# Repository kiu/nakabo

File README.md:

# nakabo

Welcome to *nakabo* - a collection of neatly designed breakout boards aimed at simplifying development and experimentation.

Feel free to give me a shoutout [@kiu112](https://twitter.com/kiu112) - I would love to see how my [#nakabo](https://twitter.com/search?q=%2523nakabo) boards are being used in your projects.

# nakabo-avr64*

* All pins routed out to headers / sockets
* AVR6 IDC connector (6P 2x03 2.54mm / 100mil) for UPDI programming and debugging
* Major pin functions documented on front silkscreen
* 2.54mm / 100mil breadboard compatible spacing
* Dedicated reset button
* [FT232RL module](https://www.amazon.de/s?k=FT232RL+module) compatible pin socket for easy serial interfacing

Disclaimer: These are not plug and play development boards - you need an UPDI compatible programmer to use them. There is no protection (e.g. reverse polarity), handle with care.

## nakabo-avr64da32

*nakabo-avr64da32* is a break-out board for the [AVR64DA32](https://www.microchip.com/en-us/product/AVR64DA32) microcontroller.

(Hint: stencil is identical to *nakabo-avr64ea32*)

## nakabo-avr64db32

*nakabo-avr64db32* is a break-out board for the [AVR64DB32](https://www.microchip.com/en-us/product/AVR64DB32) microcontroller.

(Hint: stencil is identical to *nakabo-avr64dd32*)

## nakabo-avr64dd32

*nakabo-avr64dd32* is a break-out board for the [AVR64DD32](https://www.microchip.com/en-us/product/AVR64DD32) microcontroller.

(Hint: stencil is identical to *nakabo-avr64db32*)

## nakabo-avr64ea32

*nakabo-avr64ea32* is a break-out board for the [AVR64EA32](https://www.microchip.com/en-us/product/AVR64EA32) microcontroller.

(Hint: stencil is identical to *nakabo-avr64da32*)

# License

This project is licensed under the Creative Commons Attribution-NonCommercial 3.0 Unported (CC BY-NC 3.0) license.

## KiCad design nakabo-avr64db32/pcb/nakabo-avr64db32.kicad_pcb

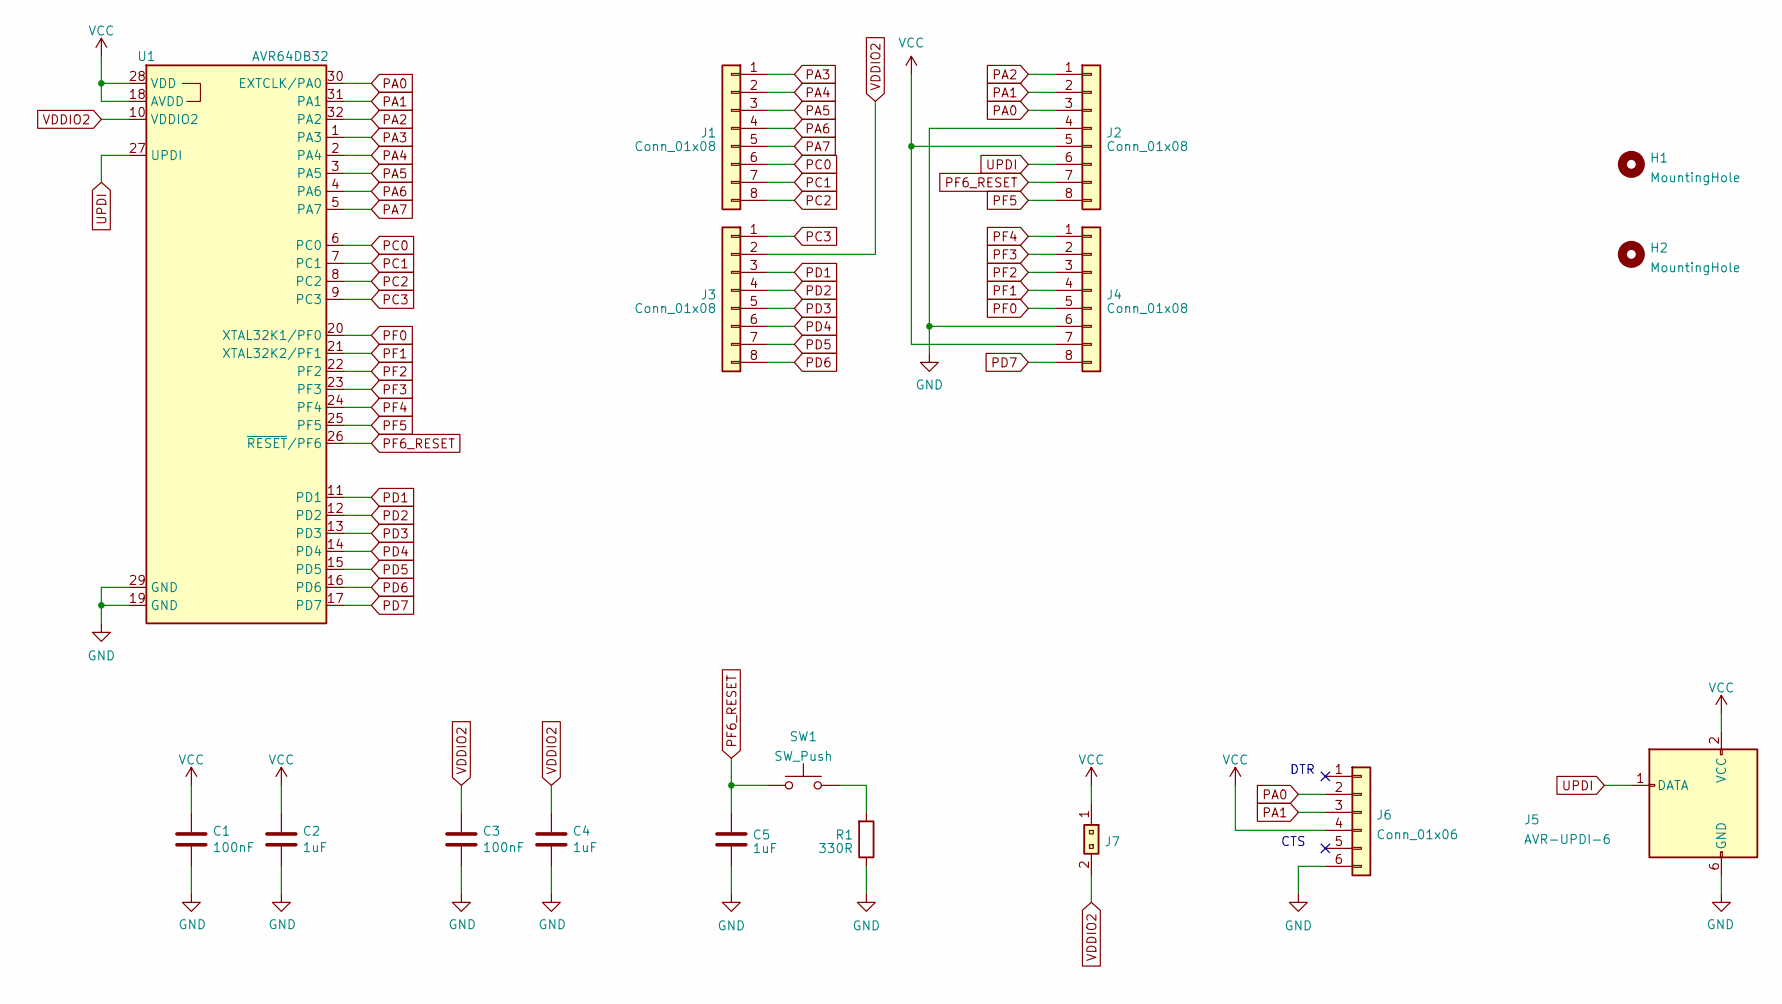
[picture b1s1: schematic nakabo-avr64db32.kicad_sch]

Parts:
C1, C3: 100nF; C_0805_2012Metric
C2, C4, C5: 1uF; C_0805_2012Metric
H1, H2: MountingHole; MountingHole_3.2mm_M3_DIN965
J1, J2, J3, J4: Conn_01x08; PinSocket_1x08_P2.54mm_Vertical
J5: AVR-UPDI-6; IDC-Header_2x03_P2.54mm_Vertical
J6: Conn_01x06; PinSocket_1x06_P2.54mm_Vertical
J7: 1x02_Jumper; PinHeader_1x02_P2.54mm_Vertical
R1: 330R; R_0805_2012Metric
SW1: SW_Push; SW_Push_1P1T_NO_4.5x4.5mm
U1: AVR64DB32; TQFP-32_7x7mm_P0.8mm

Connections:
GND: C1.2, C2.2, C3.2, C4.2, C5.2, J2.4, J4.6, J5.6 (GND), J6.6, R1.1, U1.19 (GND), U1.29 (GND)
unnamed: R1.2, SW1.2
PA0: J2.3, J6.2, U1.30 (EXTCLK/PA0)
PA1: J2.2, J6.3, U1.31 (PA1)
PA2: J2.1, U1.32 (PA2)
PA3: J1.1, U1.1 (PA3)
PA4: J1.2, U1.2 (PA4)
PA5: J1.3, U1.3 (PA5)
PA6: J1.4, U1.4 (PA6)
PA7: J1.5, U1.5 (PA7)
PC0: J1.6, U1.6 (PC0)
PC1: J1.7, U1.7 (PC1)
PC2: J1.8, U1.8 (PC2)
PC3: J3.1, U1.9 (PC3)
PD1: J3.3, U1.11 (PD1)
PD2: J3.4, U1.12 (PD2)
PD3: J3.5, U1.13 (PD3)
PD4: J3.6, U1.14 (PD4)
PD5: J3.7, U1.15 (PD5)
PD6: J3.8, U1.16 (PD6)
PD7: J4.8, U1.17 (PD7)
PF0: J4.5, U1.20 (XTAL32K1/PF0)
PF1: J4.4, U1.21 (XTAL32K2/PF1)
PF2: J4.3, U1.22 (PF2)
PF3: J4.2, U1.23 (PF3)
PF4: J4.1, U1.24 (PF4)
PF5: J2.8, U1.25 (PF5)
PF6_RESET: C5.1, J2.7, SW1.1, U1.26 (~RESET/PF6)
UPDI: J2.6, J5.1 (DATA), U1.27 (UPDI)
VCC: C1.1, C2.1, J2.5, J4.7, J5.2 (VCC), J6.4, J7.1, U1.18 (AVDD), U1.28 (VDD)
VDDIO2: C3.1, C4.1, J3.2, J7.2, U1.10 (VDDIO2)

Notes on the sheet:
DTR
CTS

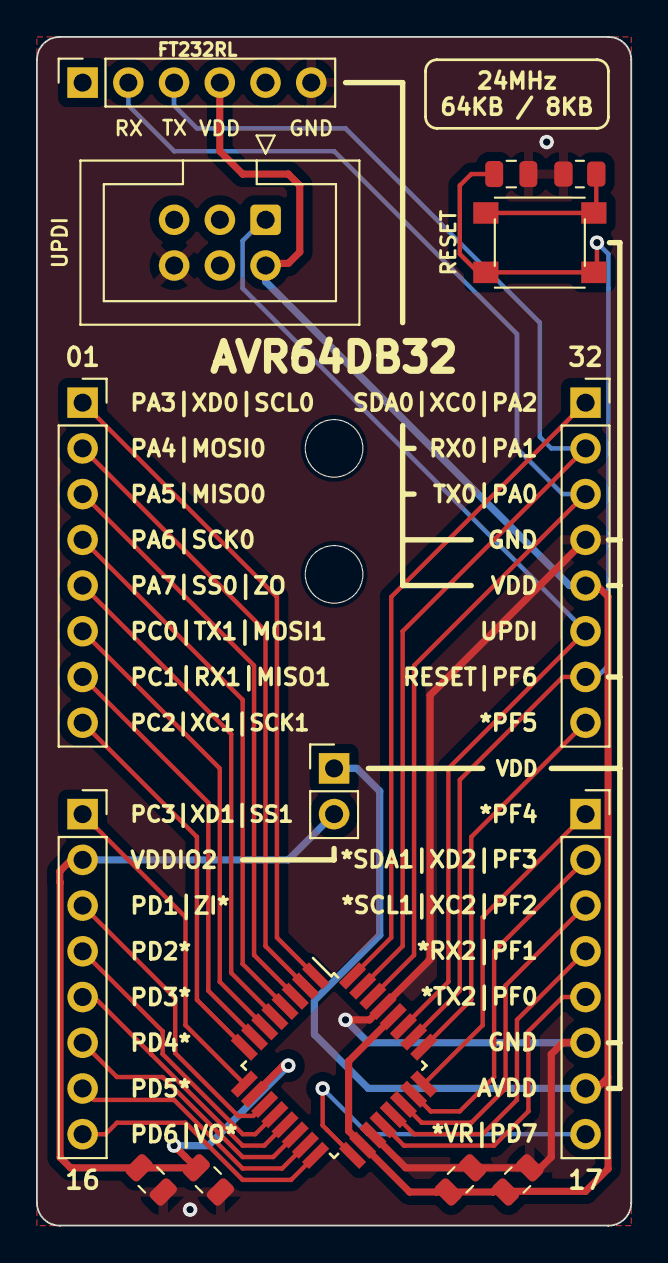
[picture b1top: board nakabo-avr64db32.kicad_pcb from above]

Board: 2 copper layers, 33.0 x 66.0 mm, 17 parts (0 on the bottom side), 31 nets.

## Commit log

2023-03-30 Init.
2023-04-14 Adding Hello World to nakabo-avr64*
2023-04-14 Why is the kicad default .gitignore ignoring *.xml?
2023-04-28 Added images
